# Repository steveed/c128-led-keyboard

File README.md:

# c128-led-keyboard

A mechanical keyboard for the Commodore 128 with a microcontroller on board: an ESP32-S3
scans the switches and presents them to the C128 through a CH446Q analog crosspoint, so the
computer sees an ordinary keyboard matrix while the board adds per-key RGB lighting, lock
keys that remember their state, a rear-exit connector in stock C128 pin order and, later, a
command layer, USB keyboard mode and a network keyboard.

The plate, a 1.5 mm aluminum PCB with stabilizer slots for a 9u or a 6.25u spacebar:

Renders are regenerated by GitHub Actions whenever the board or plate changes on `main`
(`make render` does the same locally, in KiCad's container).

Status (2026-11-23): schematic passing ERC; **board laid out, fully routed and DRC clean**,
with the JLCPCB order files (gerbers, BOM, placement) generated and checked in the fab's
placement preview; plate ready as one aluminum board that takes either spacebar.  Quoted at
about 500 USD for five assembled boards shipped, plus about 50 USD for the plate; not ordered
yet.  Bench firmware runs on a devkit; the bench proofs have not started.  The plan and its reasoning are in [docs/rev3-plan.md](docs/rev3-plan.md).

## What is here

| folder | what |
|---|---|
| [`pcb/`](pcb/README.md) | KiCad 10 project for the board (generated schematic, BOM), the plate as an aluminum-PCB board (takes a 9u or a 6.25u spacebar), JLCPCB order files, bench notes for proving the circuit |
| [`layout/`](pcb/README.md#layout-data) | the switch positions, matrix nets and plate outline every generator reads |
| [`firmware/`](firmware/README.md) | ESP-IDF project for the ESP32-S3, built in Docker, with a Wokwi simulation |
| [`printables/`](printables/spacebar_offset_adapter/README.md) | the spacebar offset adapter: the C128's own spacebar on the board's 9u stabilizers |
| [`keycaps/`](keycaps/README.md) | legend map, front-legend artwork and vendor notes for an MX keycap set, and the 9u spacebar drawing |
| [`docs/`](docs/) | the rev 3 plan, a part-by-part circuit walkthrough, and the rev 2.3 issues that motivated it |

The case for the 128D / DCR external keyboard is its own project,
[c128d-keyboard-case](https://github.com/steveed/c128d-keyboard-case).

## Where the measurements come from

This board is new, but the keyboard it describes is not.  The key positions, the C128 matrix
assignment of every key and the plate are, for now, the measurements of the rev 2.3 board and
plate from [the-c128-keyboard-project](https://codeberg.org/jflitton/the-c128-keyboard-project).
They were extracted once into `layout/switches.json` and `layout/plate.json`, and nothing here
reads the original files.  When the new board is laid out, `pcb/tools/extract_layout.py`
re-extracts the switches from it and the plate, firmware keymap and schematic follow; see
[pcb/README.md](pcb/README.md#layout-data).

## Parts from the original project

Some pieces are used as they are and are not copied here:

- keycap adapters for reusing the original Mitsumi caps on MX-style switches, switch shims,
  and the keyboard cable ends:
  [`printable_parts/`](https://codeberg.org/jflitton/the-c128-keyboard-project/src/branch/main/printable_parts)
- the original steel plate for laser cutting:
  [`plate/plate.step`](https://codeberg.org/jflitton/the-c128-keyboard-project/src/branch/main/plate/plate.step)
- the rev 2.3 passive board, which the bench notes use as a test bed:
  [`pcb/`](https://codeberg.org/jflitton/the-c128-keyboard-project/src/branch/main/pcb)

## Datasheets

- CH446Q analog crosspoint (WCH): <https://www.wch-ic.com/downloads/CH446DS1_PDF.html>
- M5Stack NeoPixel / RGB LED units (SK6812), used on the bench:
  <https://docs.m5stack.com/en/unit/neopixel>, <https://docs.m5stack.com/en/unit/rgb>
- Every part the board's footprints, pinouts and fab placement were checked against:
  [pcb/datasheets/README.md](pcb/datasheets/README.md)

## License and credits

This project is a fork of
[the-c128-keyboard-project](https://codeberg.org/jflitton/the-c128-keyboard-project) by
Jeff Flitton, whose PCB was in turn based on the
[original C128 keyboard PCB](https://codeberg.org/jgrip/c128-keyboard) by Johan Grip, maker
of the [C128 Neo](https://c128.se/).  The key layout, matrix assignment and plate
measurements in `layout/`, and everything generated from them, derive from Jeff Flitton's
rev 2.3 board and plate.  The rev 3 circuit, generators, firmware, keycap work and
documentation were written for this repository; none of it is part of the upstream
project, and this project is not endorsed by its authors.

Released, like the project it builds on, under
[Creative Commons Attribution-ShareAlike 4.0 International](LICENSE.md): you may copy,
modify and sell it, including boards and kits, provided you credit the authors, link back,
say what you changed, and release adaptations under the same license.  It is provided as
is, without warranties; see the license for the disclaimer.

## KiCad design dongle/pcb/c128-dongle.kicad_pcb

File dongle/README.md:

# C128D wireless dongle

A small board that plugs into the 128D's keyboard socket (on the computer's right side) and
passes the keyboard straight through.  An ESP32-S3 on it drives a CH446Q crosspoint on the
host lines, so keys can come from the rev 3 keyboard over the radio, from an app on a Mac
(USB-C), or from a USB keyboard (USB-A).  The plan and every decision behind it are in
[docs/wireless-128d.md](../docs/wireless-128d.md).

Status (2026-11-27): **schematic generated and ERC-clean; footprints drawn; board placed and
routed (autorouted, the USB nets at J1 and U5 finished by hand); DRC clean and matching the
schematic; firmware not started.**

## Files

| File | What |
|---|---|
| `pcb/tools/gen_sch.py` | writes the schematic: `c128-dongle.kicad_sch`, `mcu.kicad_sch`, `host.kicad_sch`, the project symbol library and both library tables |
| `pcb/c128-dongle.kicad_sch` | root sheet |
| `pcb/mcu.kicad_sch` | ESP32-S3-MINI-1, USB-C and USB-A behind the CH442E switch, the SY6280AAC USB-A power switch, the 5 V entry and the 3.3 V LDO, status LED, buttons, UART pads |
| `pcb/host.kicad_sch` | the keyboard's crosspoint circuit (CH446Q, lock-line and RESTORE FETs, sense diode, LED buffer) and the two DB25s |
| `pcb/c128rev3.kicad_sym`, `pcb/sym-lib-table` | project symbols: CH446Q, CH442E, SY6280AAC |
| `pcb/fp-lib-table` | the keyboard's footprint library (for the USB-C) and `dongle.pretty` |
| `pcb/tools/gen_board.py` | writes `c128-dongle.kicad_pro` and `.kicad_dru` from the keyboard's (same rules, the dongle's sheets and power nets), and once the 65 x 45 mm 4-layer board with its outline; it will not overwrite the board |
| `pcb/c128-dongle.kicad_pro`, `.kicad_dru`, `.kicad_pcb` | the project, its J1 USB-C rule, and the board (hand-edited from here: F8 brings the parts in) |
| `pcb/tools/gen_fp.py` | writes the two edge-straddle DB25 footprints into `dongle.pretty` |
| `pcb/dongle.pretty/` | the USB-A (JLCPCB's own C8328 footprint, via easyeda2kicad 1.0.1, checked against the datasheet; peg holes made non-plated, shell pads named SH) and the two DB25s (from `gen_fp.py`) |

## The schematic is generated

```
docker compose run --rm -e KICAD_SYMBOLS=/usr/share/kicad/symbols kicad python3 dongle/pcb/tools/gen_sch.py
```

Change the script, not the sheets: every run rewrites them.  The host side is not copied from
the keyboard but called: the script imports `pcb/tools/gen_sch.py` and runs its
`crosspoint_core()`, so the CH446Q, the FETs, the sense diode and the LED buffer are the same
parts, references and nets on both boards, on the same ESP32 pins.  The two DB25s take their
pin assignment from the keyboard's `HOST_PINS` table, converted to D-sub numbering.

## The DB25 footprints

`docker compose run --rm kicad python3 dongle/pcb/tools/gen_fp.py` writes both, from FCI drawing
C-DSUB-0064 (`pcb/datasheets/FCI-C-DSUB-0064.pdf`), size 25: 2.76 mm pitch, 2.84 mm between the
cup rows (a 1.6 mm board fits between them), cups about 7.4 mm behind the insulator.

- Pins 1-13 on F.Cu, pins 14-25 on B.Cu, offset half a pitch; pads 1.5 x 4.5 mm from 0.4 mm
  inside the board edge (y = 0 in the footprint; the connector hangs off at y < 0).
- Seen from the solder side with the 13-pin row on top, a plug has pin 1 on the right and a
  socket on the left, so `DB25_Pins_*` (J2) has pin 1 at +x and `DB25_Socket_*` (J3) at -x.
- The D shell goes in one way only, so the 128D's socket decides which way up the dongle
  sits: with its 13-pin row at the top, the dongle's F.Cu face is up.
- Fab: insulator, flange with its jackscrew holes (47.04 mm apart) and the D shell; a dashed
  line on Dwgs.User marks the board edge.

## The board

- **Outline:** 65 x 45 mm (widened from 60 on 2026-11-27 for room round U5 and the USB-C pair), 1 mm corners; DB25s on the west and east edges, USB on the north,
  the ESP32's antenna over the south edge (`gen_board.py`).
- **Stackup:** F.Cu signals and ICs; In1.Cu a solid GND plane; In2.Cu a third signal layer;
  B.Cu signals and the discretes.  +3V3 runs as 0.5 mm tracks.  With In2 as a +3V3 plane
  instead, the 25 straight-through DB25 lines and the CH446Q's 19 left 21-28 nets that would
  not route on two signal layers; with three, only the USB nets at J1 and the CH442E were left
  (the USB-C's A/B crossing is hand-routed, as on the keyboard).
- **Placement:** the connectors, the ESP32, the buttons and the status LED placed by hand and
  locked; the rest by KiCadRoutingTools' placer (`krt` container) with ICs on top and the
  resistors, capacitors, transistors and diodes underneath at 0 or 90 degrees, each IC's
  decaps under it.  Seed 0 of 12 (second round, `build/placement-dongle/round2/`, not
  committed), judged by a quick route; Q2 then moved clear of J3's courtyard, which the
  placer's legality check missed.
- **Silkscreen:** `docker compose run --rm kicad python3 pcb/tools/silk.py
  dongle/pcb/c128-dongle.kicad_pcb` (the keyboard's tool) moved the references DRC flagged,
  put TP2's, R1's and LED1's pin-1 mark on the fab layer (no clear spot near them), and trimmed
  J4's flange and U1's antenna outline where they run past the board edge, and J4's lines over
  its shield pads.  So J4 no longer matches its library copy (a DRC warning): don't update it
  from the library, or rerun `silk.py` after.
- **In1 is the plane only:** after hand routing, check nothing landed on In1 and no via is
  blind (both happened once).  GND is in the Power class, 0.5 mm: pick 0.25 mm before routing
  from U5's 0.35 mm GND pads, or the router won't start.
- **Connector clearances:** J4 (USB-A) at x 123 and J1 (USB-C) at x 146 leave 8.3 and 3.3 mm
  to the DB25 pad strips; the buttons are turned 90 degrees for 3.6 mm.  J4's EasyEDA courtyard
  did not cover its shell tabs and was widened.

## Ordering

```
docker compose run --rm -e KICAD_CLI=kicad-cli kicad python3 pcb/tools/fab.py dongle/pcb/c128-dongle.kicad_pcb
```

writes `dongle/pcb/fab/` (untracked): the gerbers zip, BOM and CPL, as for the keyboard (see
`pcb/README.md`).  J2 and J3, the DB25s, are left to the builder.  Order a 4-layer board with
assembly on both sides.  Rotations were checked in JLCPCB's placement preview on 2026-11-27: the
bottom side as written, the top with the corrections in `fab.py`'s `ROT_ADD_TOP` (U2-U8).
U3's and U5's turn ("right 90" in the preview, taken as clockwise) is still to be confirmed on
the next upload.  Quoted that day for five: about 175 USD for boards and assembly, plus 127 USD
shipping and tariffs; to be ordered with the keyboard's next order to share the shipping.

## Parts this board adds

LCSC numbers are in the script; check each on lcsc.com before ordering.

| Part | LCSC | Datasheet checked |
|---|---|---|
| ESP32-S3-MINI-1-N8 (PCB antenna) | C2913206 | |
| WCH CH442E, USB 2.0 2:1 switch | C150097 | `pcb/datasheets/C150097.pdf` (WCH CH440/CH442 v3B): pins, select polarity, runs at 3.3 V |
| Silergy SY6280AAC, USB-A power switch | C55136 | `pcb/datasheets/C55136.pdf` (preliminary rev 0.3): pins, Ilim = 6800 / Rset, EN active high |
| USB-A receptacle, right angle (Jing Extension 904-131A2032S10100) | C8328 | `pcb/datasheets/C8328.pdf`: pins, outline, PCB layout (signal-pad width not dimensioned) |
| UNI-ROYAL 12 k, 0603, 1 % (the SY6280's Rset, about 0.57 A) | C22790 | `pcb/datasheets/C22790.pdf` (series sheet); value from the LCSC page |
| DB25 male and female, solder cup | none | hand-soldered; straddle 1.6 mm board edges |

## Still open

- **Power:** the 128D's +5 V on the keyboard socket feeds the dongle, with the ESP32's radio
  peaks and a USB keyboard on top of the keyboard's own draw.  Measure what the 128D's
  keyboard 5 V delivers before relying on it without the USB-C.
- **Routing:** KiCadRoutingTools' router (`krt`): `route_diff.py` for the three USB pairs, then
  `route.py` on F.Cu, In2 and B.Cu at the board's rules (`--escalation board
  --no-fix-drc-settings`).  It cannot do the USB-C pair at J1 legally: J1's D+/D- pads are 0.3 mm
  wide, and the pair pass drops a 0.3/0.15 mm via into the pad to change layers (its own log calls
  it an advanced-tier fab floor), so that pair is hand-routed, with the A6/B6 and A7/B7 crossing.
  U5 sits between the USB-A and the USB-C, just in from the north edge (139, 83), where its
  lines to both ports are shortest.  The USB-C pair's layer change beside J1, its A7/B7 crossing
  and the last stubs into U5 were routed by hand.
- **Firmware:** the dongle app, sharing the keyboard firmware's crosspoint driver.

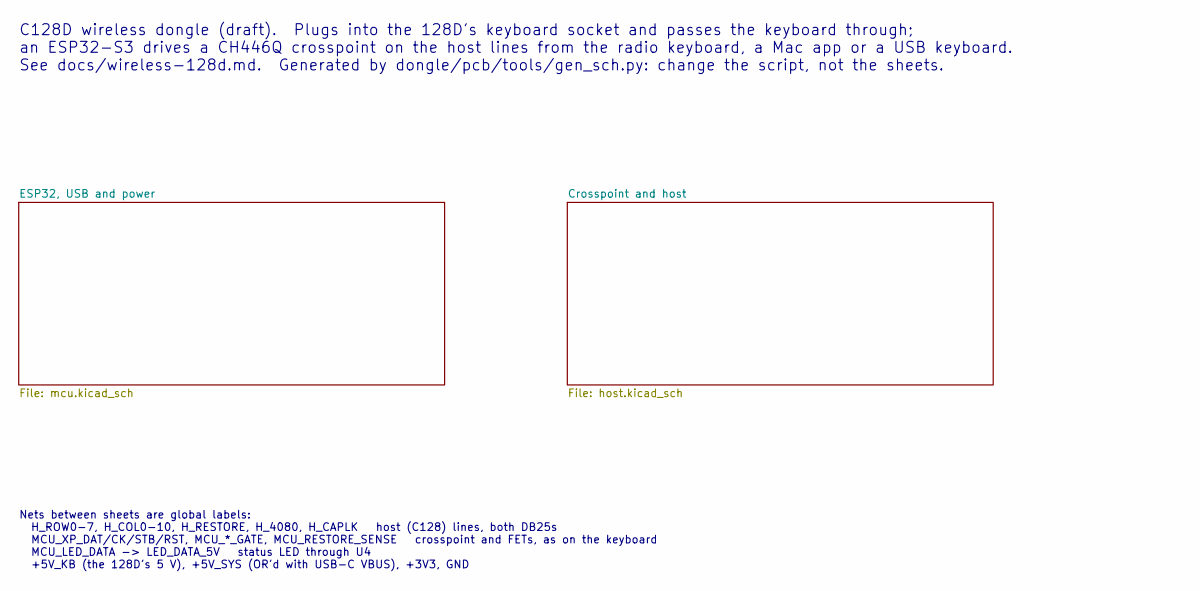
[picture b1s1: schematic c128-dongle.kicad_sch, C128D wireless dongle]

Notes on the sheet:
C128D wireless dongle (draft). Plugs into the 128D's keyboard socket and passes the keyboard through; an ESP32-S3 drives a CH446Q crosspoint on the host lines from the radio keyboard, a Mac app or a USB keyboard. See docs/wireless-128d.md. Generated by dongle/pcb/tools/gen_sch.py: change the script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
Nets between sheets are global labels: H_ROW0-7, H_COL0-10, H_RESTORE, H_4080, H_CAPLK host (C128) lines, both DB25s MCU_XP_DAT/CK/STB/RST, MCU_*_GATE, MCU_RESTORE_SENSE crosspoint and FETs, as on the keyboard MCU_LED_DATA -> LED_DATA_5V status LED through U4 +5V_KB (the 128D's 5 V), +5V_SYS (OR'd 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

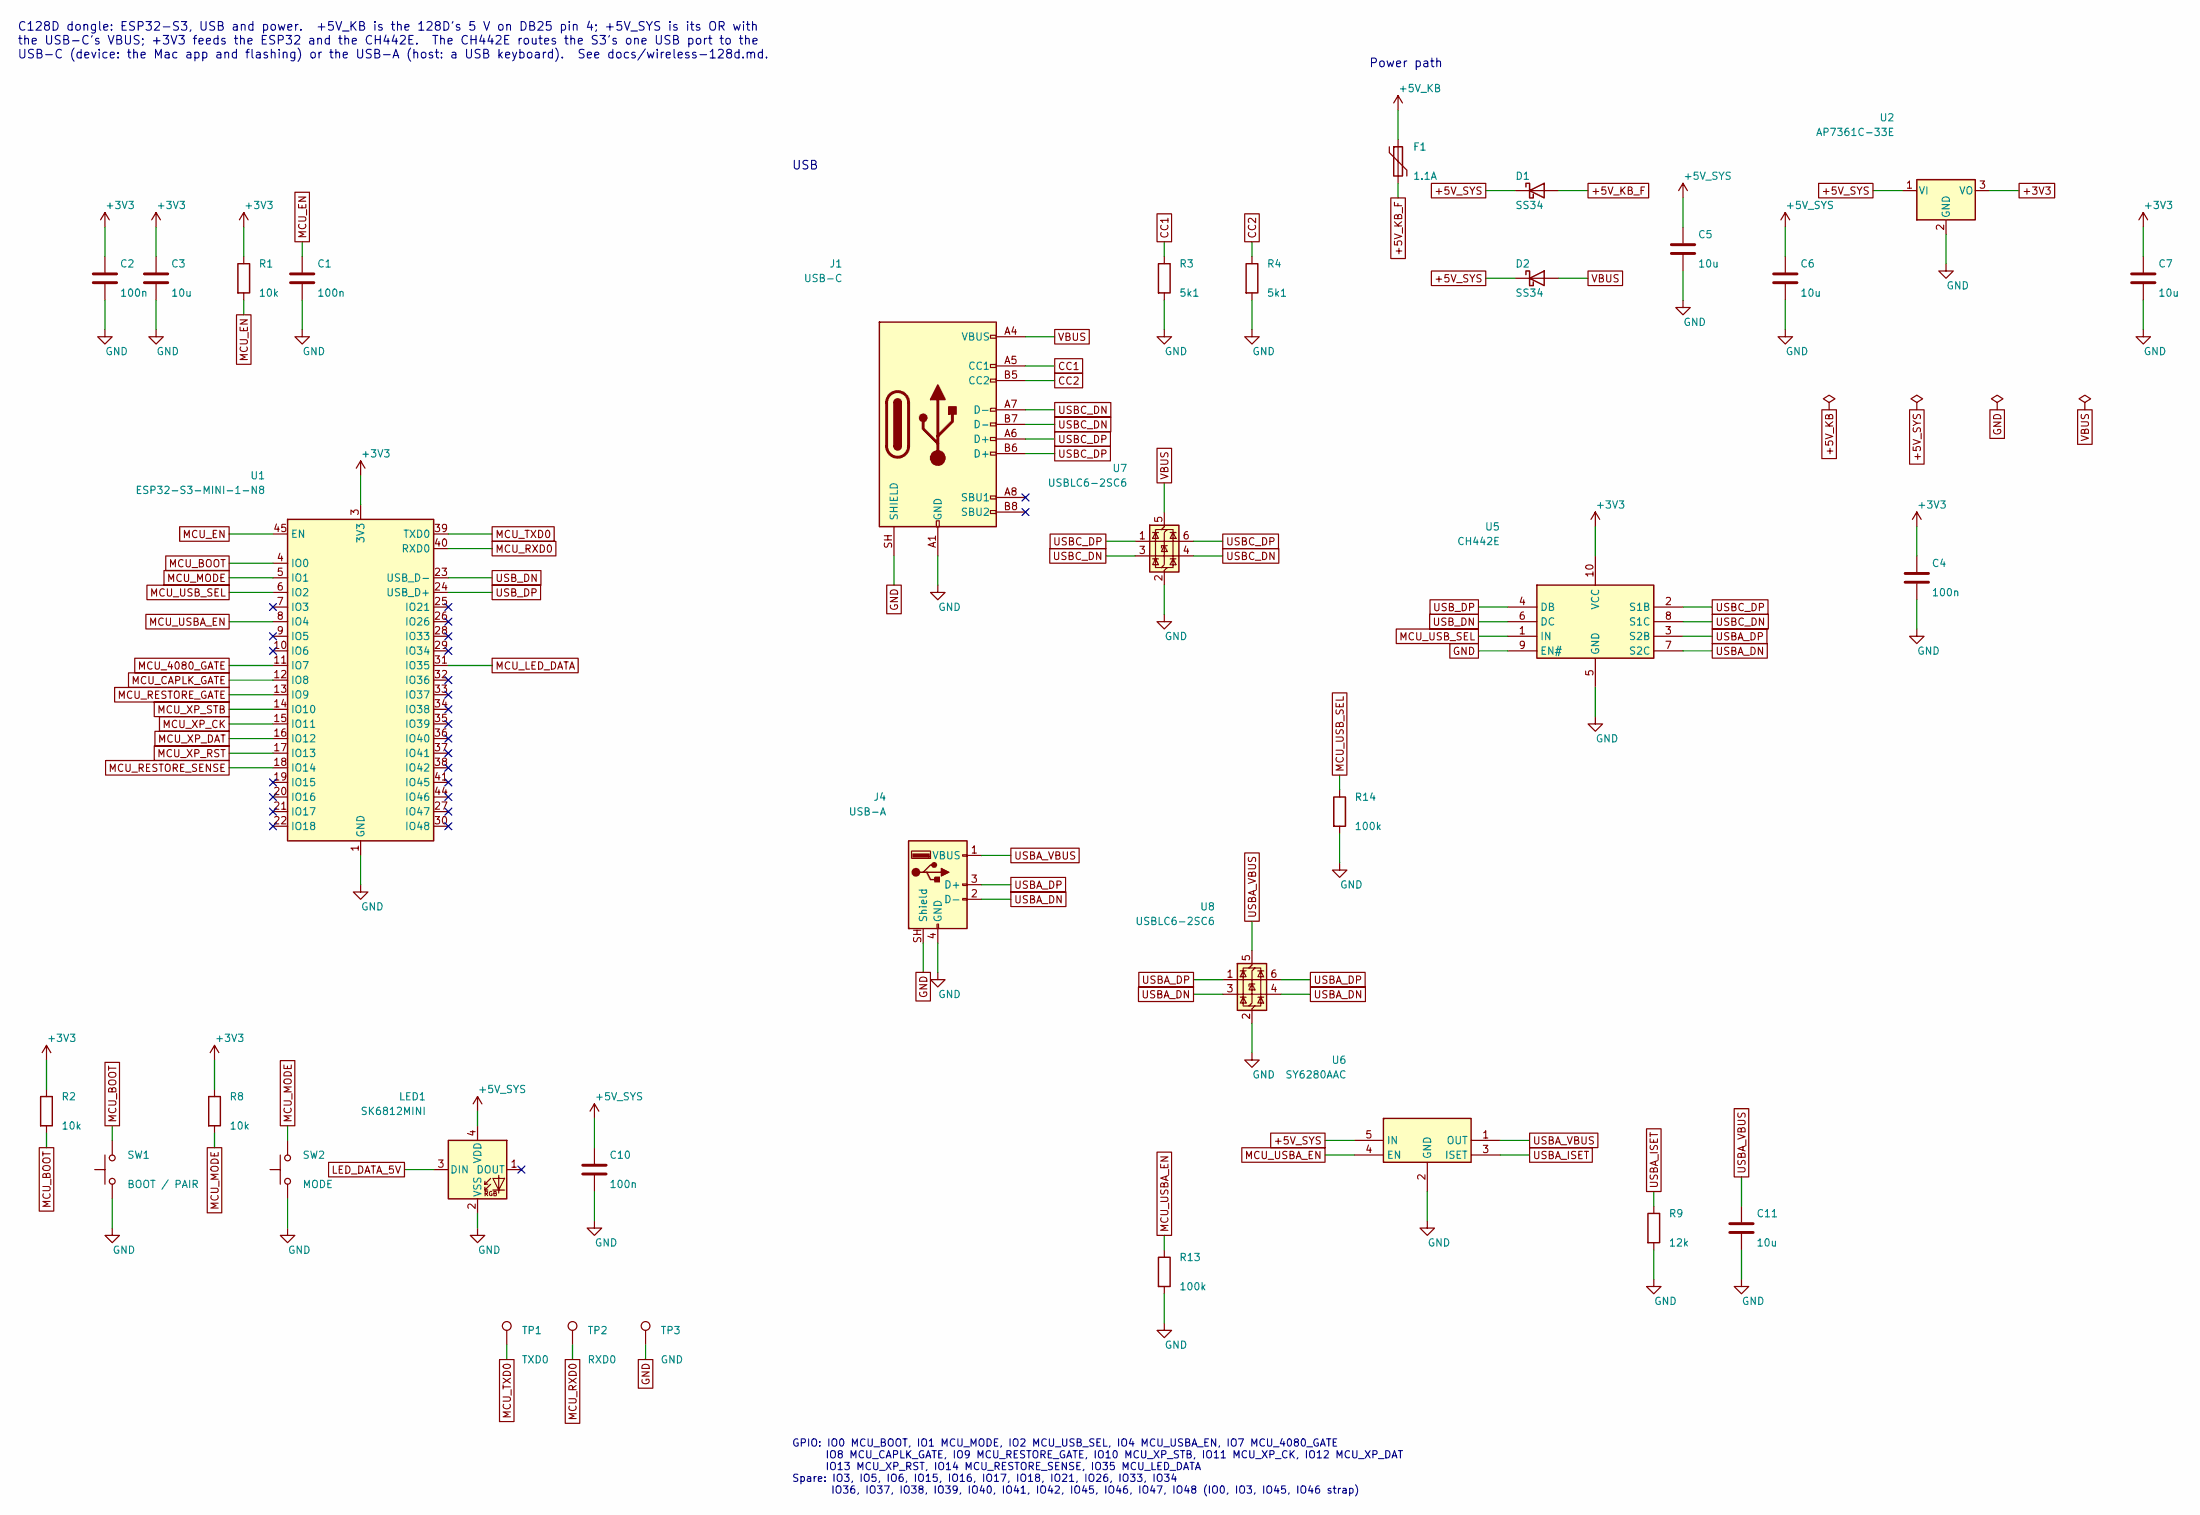
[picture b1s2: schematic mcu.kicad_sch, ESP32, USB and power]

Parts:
C1, C2, C4, C10: 100n; C_0603_1608Metric_Pad1.08x0.95mm_HandSolder; LCSC C14663
C3: 10u; C_0603_1608Metric_Pad1.08x0.95mm_HandSolder; LCSC C19702
C5, C6, C7, C11: 10u; C_1206_3216Metric_Pad1.33x1.80mm_HandSolder; LCSC C13585
D1, D2: SS34; D_SMA; LCSC C8678
F1: 1.1A; Fuse_1812_4532Metric; LCSC C142746
J1: USB-C; USB_C_Receptacle_ShouHan_TYPE-C-16P-3MD-040; LCSC C41417453
J4: USB-A; USB_A_Jing_904-131A2032S10100; LCSC C8328
LED1: SK6812MINI; LED_SK6812MINI_PLCC4_3.5x3.5mm_P1.75mm; LCSC C2886570
R1, R2, R8: 10k; R_0603_1608Metric_Pad0.98x0.95mm_HandSolder; LCSC C25804
R3, R4: 5k1; R_0603_1608Metric_Pad0.98x0.95mm_HandSolder; LCSC C23186
R9: 12k; R_0603_1608Metric_Pad0.98x0.95mm_HandSolder; LCSC C22790
R13, R14: 100k; R_0603_1608Metric_Pad0.98x0.95mm_HandSolder; LCSC C25803
SW1: BOOT / PAIR; SW_SPST_PTS645Sx43SMTR92; LCSC C221880
SW2: MODE; SW_SPST_PTS645Sx43SMTR92; LCSC C221880
TP1: TXD0; TestPoint_Pad_1.0x1.0mm
TP2: RXD0; TestPoint_Pad_1.0x1.0mm
TP3: GND; TestPoint_Pad_1.0x1.0mm
U1: ESP32-S3-MINI-1-N8; ESP32-S2-MINI-1; LCSC C2913206
U2: AP7361C-33E; SOT-223-3_TabPin2; LCSC C500795
U5: CH442E; MSOP-10_3x3mm_P0.5mm; LCSC C150097
U6: SY6280AAC; SOT-23-5; LCSC C55136
U7, U8: USBLC6-2SC6; SOT-23-6; LCSC C7519

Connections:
+3V3: C2.1, C3.1, C4.1, C7.1, R1.1, R2.1, R8.1, U1.3 (3V3), U2.3 (VO), U5.10 (VCC); also elsewhere on the board
+5V_KB: F1.1; also elsewhere on the board
+5V_KB_F: D1.2 (A), F1.2
+5V_SYS: C5.1, C6.1, C10.1, D1.1 (K), D2.1 (K), LED1.4 (VDD), U2.1 (VI), U6.5 (IN); also elsewhere on the board
CC1: J1.A5 (CC1), R3.1
CC2: J1.B5 (CC2), R4.1
GND: C1.2, C2.2, C3.2, C4.2, C5.2, C6.2, C7.2, C10.2, C11.2, J1.A1 (GND), J1.A12 (GND), J1.B1 (GND), J1.B12 (GND), J1.SH (SHIELD), J4.4 (GND), J4.SH (Shield), LED1.2 (VSS), R3.2, R4.2, R9.2, R13.2, R14.2, SW1.1, SW2.1, TP3.1 (1_1), U1.1 (GND), U1.2 (GND), U1.42 (GND), U1.43 (GND), U1.46 (GND), U1.47 (GND), U1.48 (GND), U1.49 (GND), U1.50 (GND), U1.51 (GND), U1.52 (GND), U1.53 (GND), U1.54 (GND), U1.55 (GND), U1.56 (GND), U1.57 (GND), U1.58 (GND), U1.59 (GND), U1.60 (GND), U1.61 (GND), U1.62 (GND), U1.63 (GND), U1.64 (GND), U1.65 (GND), U2.2 (GND), U5.5 (GND), U5.9 (EN#), U6.2 (GND), U7.2 (GND), U8.2 (GND); also elsewhere on the board
LED_DATA_5V: LED1.3 (DIN); also elsewhere on the board
MCU_4080_GATE: U1.11 (IO7); also elsewhere on the board
MCU_BOOT: R2.2, SW1.2, U1.4 (IO0)
MCU_CAPLK_GATE: U1.12 (IO8); also elsewhere on the board
MCU_EN: C1.1, R1.2, U1.45 (EN)
MCU_LED_DATA: U1.31 (IO35); also elsewhere on the board
MCU_MODE: R8.2, SW2.2, U1.5 (IO1)
MCU_RESTORE_GATE: U1.13 (IO9); also elsewhere on the board
MCU_RESTORE_SENSE: U1.18 (IO14); also elsewhere on the board
MCU_RXD0: TP2.1 (1_1), U1.40 (RXD0)
MCU_TXD0: TP1.1 (1_1), U1.39 (TXD0)
MCU_USBA_EN: R13.1, U1.8 (IO4), U6.4 (EN)
MCU_USB_SEL: R14.1, U1.6 (IO2), U5.1 (IN)
MCU_XP_CK: U1.15 (IO11); also elsewhere on the board
MCU_XP_DAT: U1.16 (IO12); also elsewhere on the board
MCU_XP_RST: U1.17 (IO13); also elsewhere on the board
MCU_XP_STB: U1.14 (IO10); also elsewhere on the board
USBA_DN: J4.2 (D-), U5.7 (S2C), U8.3 (I/O2), U8.4 (I/O2)
USBA_DP: J4.3 (D+), U5.3 (S2B), U8.1 (I/O1), U8.6 (I/O1)
USBA_ISET: R9.1, U6.3 (ISET)
USBA_VBUS: C11.1, J4.1 (VBUS), U6.1 (OUT), U8.5 (VBUS)
USBC_DN: J1.A7 (D-), J1.B7 (D-), U5.8 (S1C), U7.3 (I/O2), U7.4 (I/O2)
USBC_DP: J1.A6 (D+), J1.B6 (D+), U5.2 (S1B), U7.1 (I/O1), U7.6 (I/O1)
USB_DN: U1.23 (USB_D-), U5.6 (DC)
USB_DP: U1.24 (USB_D+), U5.4 (DB)
VBUS: D2.2 (A), J1.A4 (VBUS), J1.A9 (VBUS), J1.B4 (VBUS), J1.B9 (VBUS), U7.5 (VBUS)

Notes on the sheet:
C128D dongle: ESP32-S3, USB and power. +5V_KB is the 128D's 5 V on DB25 pin 4; +5V_SYS is its OR with the USB-C's VBUS; +3V3 feeds the ESP32 and the CH442E. The CH442E routes the S3's one USB port to the USB-C (device: the Mac app and flashing) or the USB-A (host: a USB keyboard). See docs/wireless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
USB
Power path
GPIO: IO0 MCU_BOOT, IO1 MCU_MODE, IO2 MCU_USB_SEL, IO4 MCU_USBA_EN, IO7 MCU_4080_GATE IO8 MCU_CAPLK_GATE, IO9 MCU_RESTORE_GATE, IO10 MCU_XP_STB, IO11 MCU_XP_CK, IO12 MCU_XP_DAT IO13 MCU_XP_RST, IO14 MCU_RESTORE_SENSE, IO35 MCU_LED_DATA Spare: IO3, IO5, IO6, IO15, IO16, IO17, IO18, IO21, IO26, IO33,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

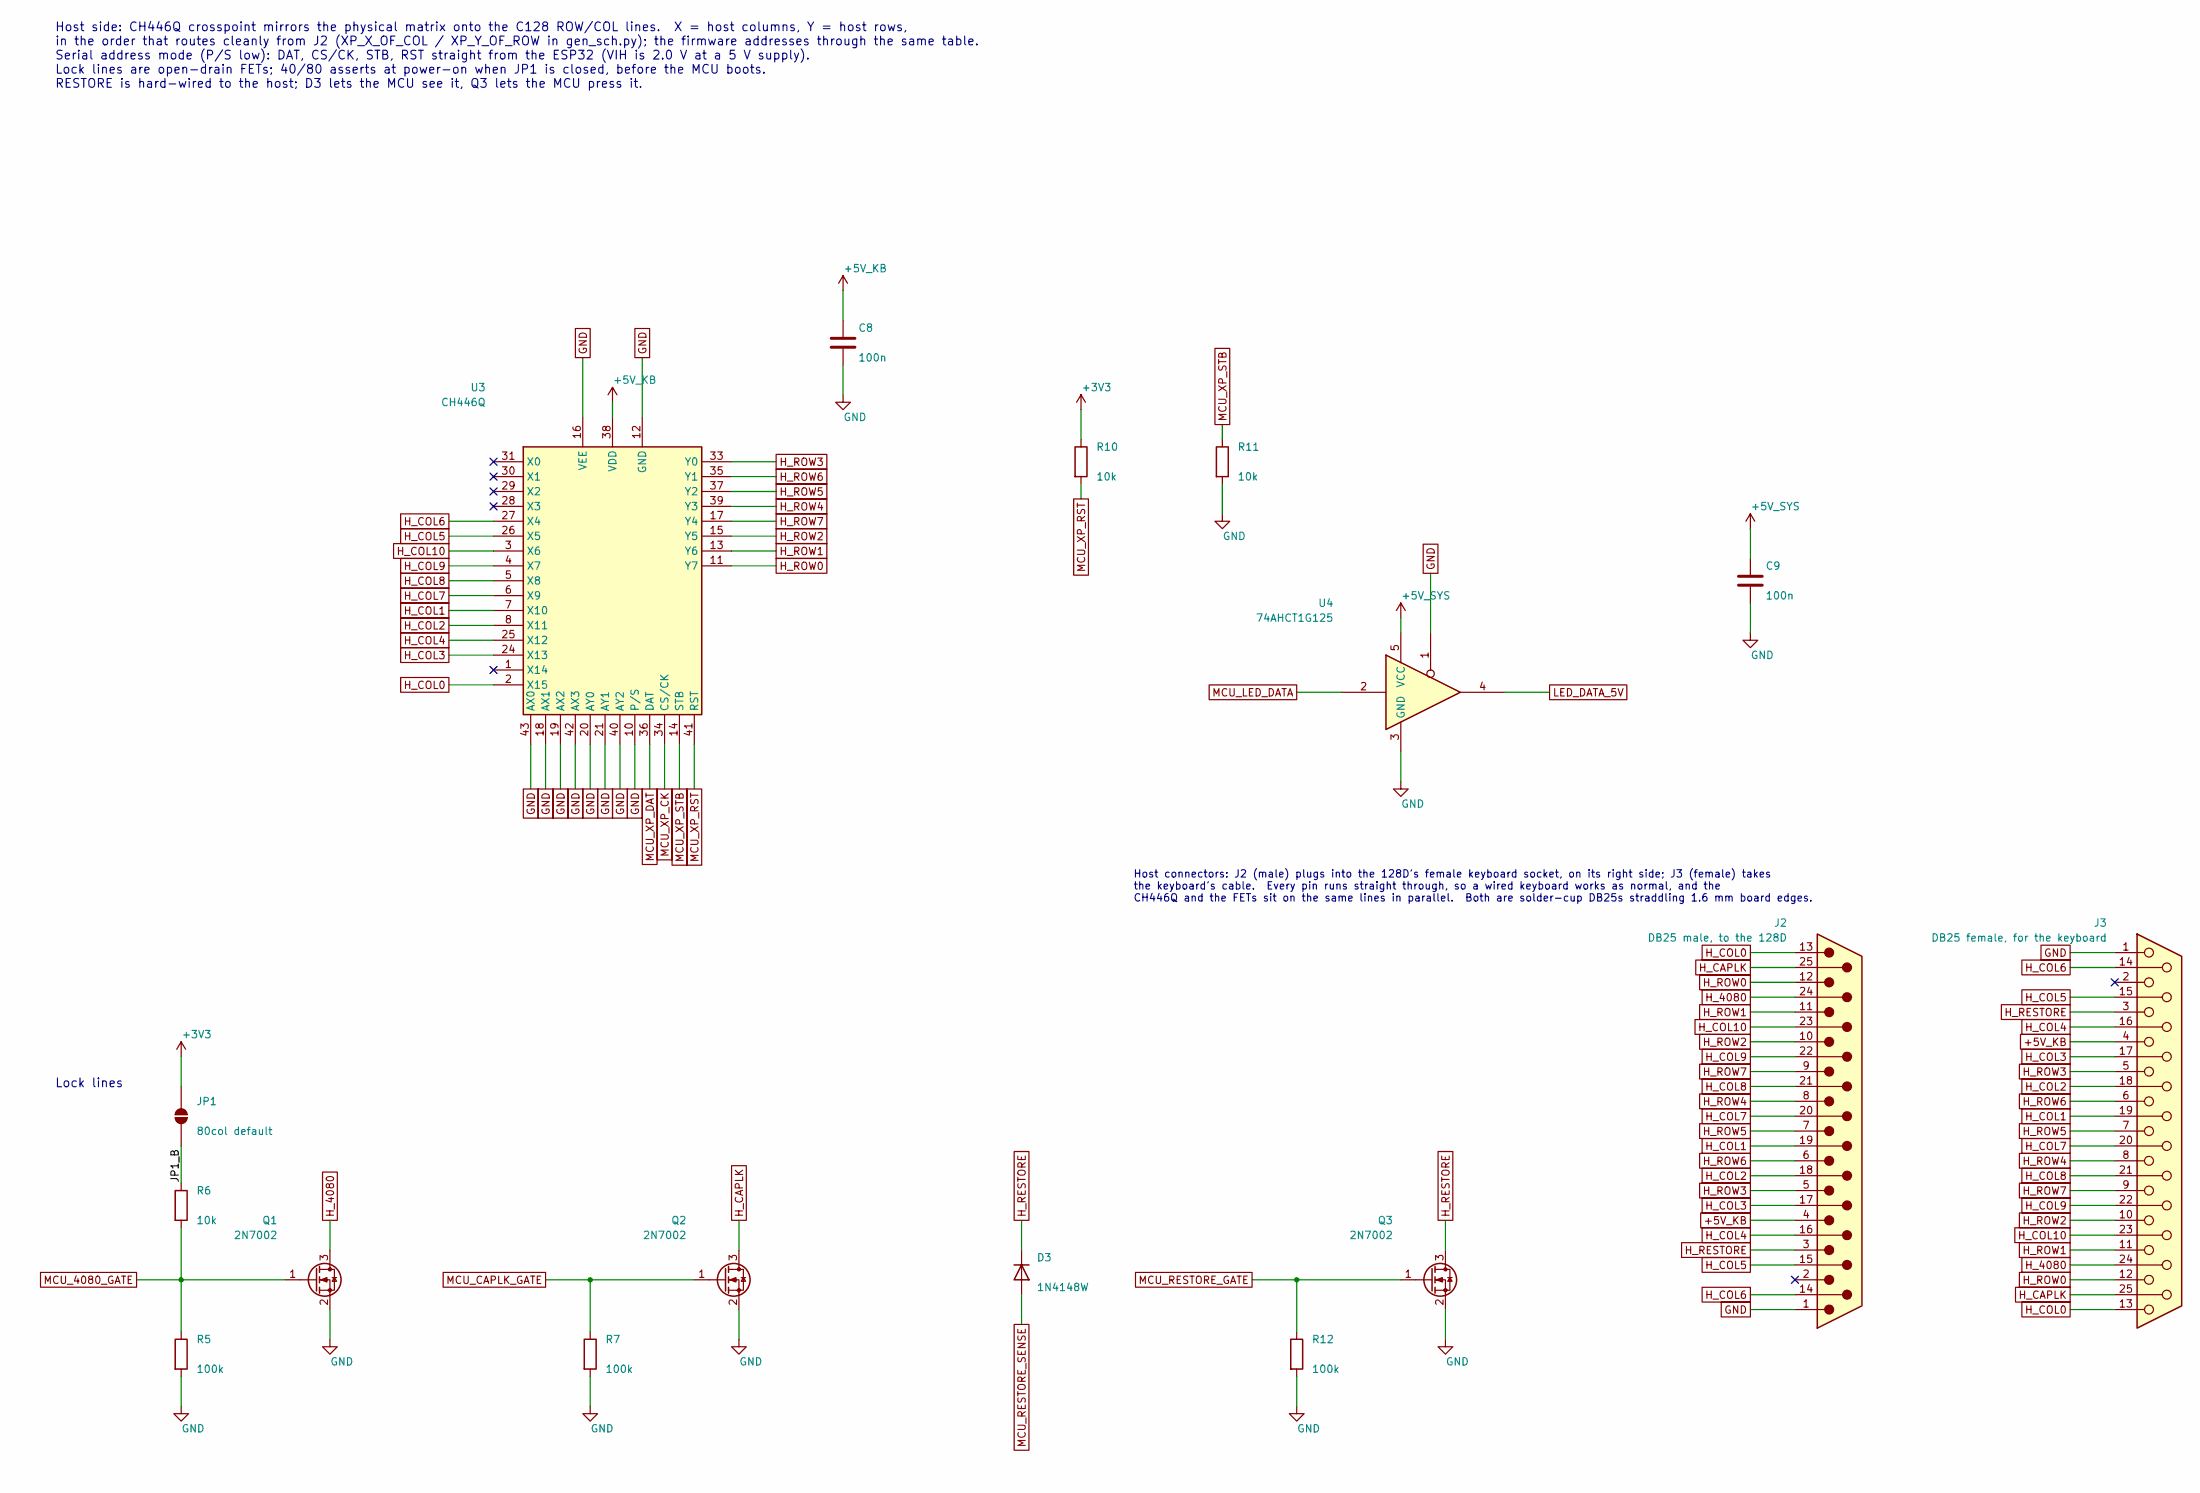
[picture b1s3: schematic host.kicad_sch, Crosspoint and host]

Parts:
C8, C9: 100n; C_0603_1608Metric_Pad1.08x0.95mm_HandSolder; LCSC C14663
D3: 1N4148W; D_SOD-123; LCSC C81598
J2: DB25 male, to the 128D; DB25_Pins_EdgeStraddle_1.6mm
J3: DB25 female, for the keyboard; DB25_Socket_EdgeStraddle_1.6mm
JP1: 80col default; SolderJumper-2_P1.3mm_Open_RoundedPad1.0x1.5mm
Q1, Q2, Q3: 2N7002; SOT-23; LCSC C8545
R5, R7, R12: 100k; R_0603_1608Metric_Pad0.98x0.95mm_HandSolder; LCSC C25803
R6, R10, R11: 10k; R_0603_1608Metric_Pad0.98x0.95mm_HandSolder; LCSC C25804
U3: CH446Q; LQFP-44_10x10mm_P0.8mm; LCSC C109471
U4: 74AHCT1G125; SOT-23-5; LCSC C7484

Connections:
+3V3: JP1.2 (B), R10.1; also elsewhere on the board
+5V_KB: C8.1, J2.4, J3.4, U3.38 (VDD); also elsewhere on the board
+5V_SYS: C9.1, U4.5 (VCC); also elsewhere on the board
/Crosspoint and host/JP1_B: JP1.1 (A), R6.1
GND: C8.2, C9.2, J2.1, J3.1, Q1.2 (S), Q2.2 (S), Q3.2 (S), R5.2, R7.2, R11.2, R12.2, U3.10 (P/S), U3.12 (GND), U3.16 (VEE), U3.18 (AX1), U3.19 (AX2), U3.20 (AY0), U3.21 (AY1), U3.40 (AY2), U3.42 (AX3), U3.43 (AX0), U4.1, U4.3 (GND); also elsewhere on the board
H_4080: J2.24, J3.24, Q1.3 (D)
H_CAPLK: J2.25, J3.25, Q2.3 (D)
H_COL0: J2.13, J3.13, U3.2 (X15)
H_COL1: J2.19, J3.19, U3.7 (X10)
H_COL2: J2.18, J3.18, U3.8 (X11)
H_COL3: J2.17, J3.17, U3.24 (X13)
H_COL4: J2.16, J3.16, U3.25 (X12)
H_COL5: J2.15, J3.15, U3.26 (X5)
H_COL6: J2.14, J3.14, U3.27 (X4)
H_COL7: J2.20, J3.20, U3.6 (X9)
H_COL8: J2.21, J3.21, U3.5 (X8)
H_COL9: J2.22, J3.22, U3.4 (X7)
H_COL10: J2.23, J3.23, U3.3 (X6)
H_RESTORE: D3.1 (K), J2.3, J3.3, Q3.3 (D)
H_ROW0: J2.12, J3.12, U3.11 (Y7)
H_ROW1: J2.11, J3.11, U3.13 (Y6)
H_ROW2: J2.10, J3.10, U3.15 (Y5)
H_ROW3: J2.5, J3.5, U3.33 (Y0)
H_ROW4: J2.8, J3.8, U3.39 (Y3)
H_ROW5: J2.7, J3.7, U3.37 (Y2)
H_ROW6: J2.6, J3.6, U3.35 (Y1)
H_ROW7: J2.9, J3.9, U3.17 (Y4)
LED_DATA_5V: U4.4; also elsewhere on the board
MCU_4080_GATE: Q1.1 (G), R5.1, R6.2; also elsewhere on the board
MCU_CAPLK_GATE: Q2.1 (G), R7.1; also elsewhere on the board
MCU_LED_DATA: U4.2; also elsewhere on the board
MCU_RESTORE_GATE: Q3.1 (G), R12.1; also elsewhere on the board
MCU_RESTORE_SENSE: D3.2 (A); also elsewhere on the board
MCU_XP_CK: U3.34 (CS/CK); also elsewhere on the board
MCU_XP_DAT: U3.36 (DAT); also elsewhere on the board
MCU_XP_RST: R10.2, U3.41 (RST); also elsewhere on the board
MCU_XP_STB: R11.1, U3.14 (STB); also elsewhere on the board

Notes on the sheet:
Host side: CH446Q crosspoint mirrors the physical matrix onto the C128 ROW/COL lines. X = host columns, Y = host rows, in the order that routes cleanly from J2 (XP_X_OF_COL / XP_Y_OF_ROW in gen_sch.py); the firmware addresses through the same table. Serial address mode (P/S low): DAT, CS/CK, STB, R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
Lock lines
Host connectors: J2 (male) plugs into the 128D's female keyboard socket, on its right side; J3 (female) takes the keyboard's cable. Every pin runs straight through, so a wired keyboard works as normal, and the CH446Q and the FETs sit on the same lines in parallel. Both are solder-cup DB25s straddli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

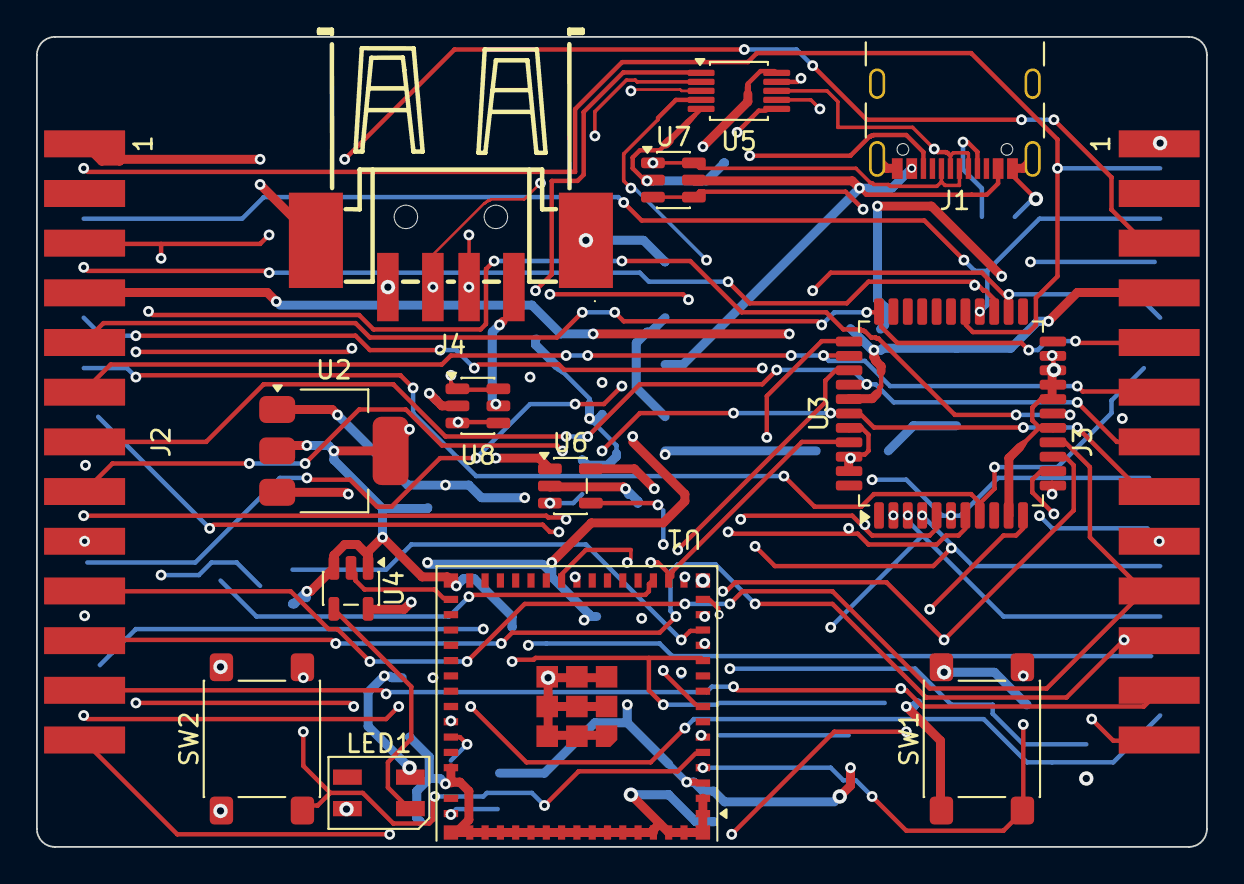
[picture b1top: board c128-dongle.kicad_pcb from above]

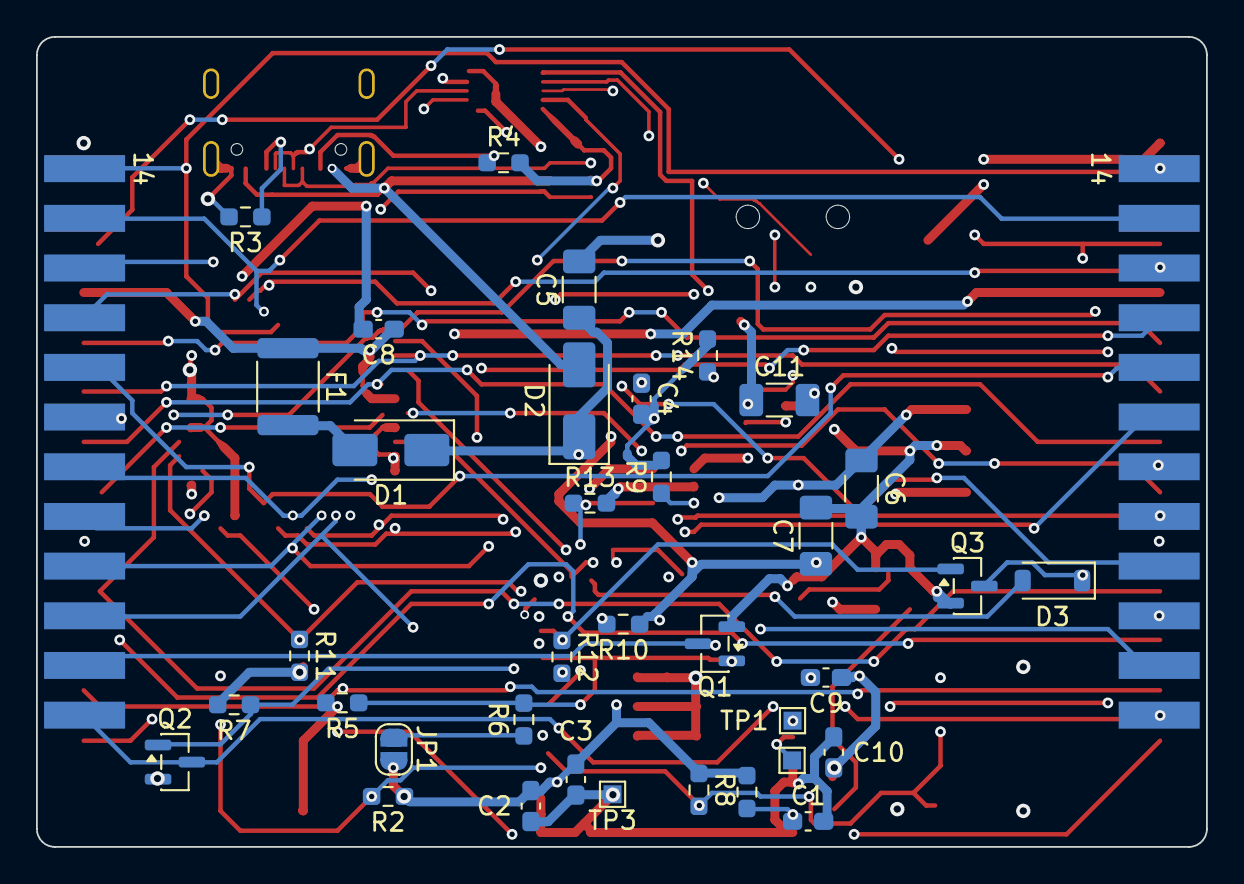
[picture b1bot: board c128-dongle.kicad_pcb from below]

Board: 4 copper layers, 65.0 x 45.0 mm, 51 parts (36 on the bottom side), 56 nets.

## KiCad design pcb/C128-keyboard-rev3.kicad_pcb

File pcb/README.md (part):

# PCB rev 3

KiCad 10 project for the smart board described in [docs/rev3-plan.md](../docs/rev3-plan.md):
ESP32-S3 module scanning the switches, a CH446Q crosspoint presenting them to the C128,
per-key SK6812 MINI lighting, saved lock state, and a rear-exit host connector in stock C128
pin order.

Status (2026-11-23): **schematic passes ERC with zero violations; the board is placed, fully
routed and tidied, with nothing unconnected, no schematic parity differences and no DRC
errors or silkscreen warnings.  The JLCPCB order files come out of `tools/fab.py`, every
SMD part has an in-stock LCSC number, and the placement rotations have been checked part by
part in JLCPCB's preview.  The dual-spacebar plate is ready to order.**  Nothing has been
ordered or built yet.
A part-by-part explanation of the circuit is in
[docs/rev3-circuit-walkthrough.md](../docs/rev3-circuit-walkthrough.md).

## Files

| File | What |
|---|---|
| `C128-keyboard-rev3.kicad_pro` / `.kicad_sch` | project and root sheet (four sub-sheets) |
| `mcu.kicad_sch` | ESP32-S3-MINI-1U-N8 (U.FL antenna), USB-C, 5 V OR-ing, AP7361C-33E LDO, buttons |
| `crosspoint.kicad_sch` | CH446Q in serial mode, 74AHCT1G125 LED-data buffer, lock-line and RESTORE FETs, RESTORE sense diode D3, host connector J2, external LED header J3 |
| `matrix.kicad_sch` | 92 switches in a 6 x 20 scanned matrix that follows the board (`tools/layout.py` `physical_matrix`), one 1N4148W per scanned key, 74HC154 plus five GPIO for the columns |
| `leds.kicad_sch` | 92 SK6812 MINI (top mount) in chain order (lock keys first) |
| `c128rev3.kicad_sym`, `sym-lib-table` | project library with the CH446Q symbol (LQFP-44 numbering) |
| `c128rev3.pretty/`, `fp-lib-table` | project footprints: MX switches (1u, 1.5u, 2u, spacebar), the SK6812 MINI for the switch LED pocket, and the USB-C receptacle |
| `datasheets/README.md` | links to the datasheets the footprints, pinouts and placement rotations were checked against; the PDFs are downloaded there by LCSC number and not tracked |
| `tools/gen_fp.py` | the generator that writes `c128rev3.pretty/` and `fp-lib-table` |
| `C128-keyboard-rev3.kicad_pcb` | the board: rev 2.3 outline, four layers, every footprint linked to the schematic, placed and routed; DRC clean |
| `tools/gen_pcb.py` | made the board's first version; the board is the source now (see *The board* below) |
| `tools/route_keys.py` | lays the regular per-key copper on the board; rerunnable (see *Routing*) |
| `tools/freeroute.py`, `tools/plane_taps.py`, `tools/clean_dangling.py` | autoroute the rest in a container; tap the inner planes from SMD pads; delete dead-end stubs (see *Routing*) |
| `tools/move.py`, `tools/swap_footprint.py`, `tools/sync_nets.py`, `tools/rip_up.py`, `tools/tidy.py`, `tools/silk.py`, `tools/to_sheet.py` | rework a routed board: move or turn parts, swap a footprint, take the schematic's nets after a change, rip up an area, tidy the router's copper, clear the silkscreen, center the board on its sheet |
| `tools/route_host.py` | lays the host lines between J2 and the CH446Q (see *Routing*) |
| `bom.csv` | grouped BOM exported from the schematic |
| `tools/fab.py`, `fab/` | the JLCPCB order files (gerber zip, BOM, placement list) and the script that writes them; `fab/` is not tracked (see *Ordering from JLCPCB*) |
| `tools/gen_sch.py`, `tools/kisym.py` | the generator that produced all of the above |
| `tools/pinmaps.json` | CH446Q LQFP-44 pin map, GPIO plan, host connector pinout |
| `bench/README.md` | shopping list and breadboard wiring to prove the design on a rev 2.3 board |
| `plate/plate-dual.kicad_pcb` | the plate to order: a KiCad board (outline polygons plus a full copper pour) for aluminum-core PCB fabrication, with stabilizer slots for both a 9u and a 6.25u spacebar; DRC clean |
| `plate/plate-9u.kicad_pcb`, `plate/plate-6.25u.kicad_pcb` | the same plate for one spacebar only |
| `plate/plate_features.json` | mounting holes, locating holes, tab slots and stabilizer cutouts in PCB coordinates, for the layout |
| `tools/plate_step.py`, `tools/gen_plate.py` | STEP reader and plate-board generator |
| `liner/` | the bottom liner: die-cut DXF, 1:1 drawing and how it fits ([liner/README.md](liner/README.md)) |
| `tools/gen_liner.py` | writes the liner from the board: outline, windows over the tall back-side parts, tape strips on bare board |
| `tools/plate_header.kicad_pcb` | the plate boards' layer stack and setup block, copied into every generated board |
| `tools/extract_layout.py`, `tools/layout.py` | write and read `../layout/`, the measurements every generator works from |

## Layout data

Every generator here, and `firmware/tools/gen_keymap.py`, reads its key positions from the
repository's `layout/` folder rather than from another board file:

- `layout/switches.json`: the 92 switches (reference, key legend, center in KiCad board
  coordinates, row and column nets).  Extracted from the rev 2.3 board,
  [`pcb/C128-keyboard.kicad_pcb`](https://codeberg.org/jflitton/the-c128-keyboard-project/src/branch/main/pcb/C128-keyboard.kicad_pcb) in the-c128-keyboard-project.
- `layout/plate.json`: the plate's outline and every cutout as line/arc loops, in the STEP
  model's own frame.  Extracted from that project's
  [`plate/plate.step`](https://codeberg.org/jflitton/the-c128-keyboard-project/src/branch/main/plate/plate.step); `gen_plate.py` fits it onto the switches.

- `layout/outline.json`: the board outline (Edge.Cuts lines and circles) from the same
  rev 2.3 board; `gen_pcb.py` drew the rev 3 outline from it.

`switches.json` also records each switch's rotation.  They are the original measurements,
used until the new board exists.  Once it is laid out,
point the extractor at it and regenerate:

```
python3 pcb/tools/extract_layout.py switches pcb/<new board>.kicad_pcb
python3 pcb/tools/gen_plate.py            # plate refits onto the new switch centers
python3 pcb/tools/gen_liner.py            # liner windows and tape follow the parts (then make liner)
python3 firmware/tools/gen_keymap.py
```

`extract_layout.py plate <file>.step` does the same for a new plate model.  Both files keep
one switch or loop per line, so a moved key is a one-line diff.

## How it was made, and how to change it

The schematic is generated: `python3 pcb/tools/gen_sch.py` rewrites every `.kicad_sch`
here.  Symbols come straight from the KiCad 10 standard libraries (derived symbols are
flattened the way eeschema does it), switch positions and matrix nets come from
`layout/switches.json` (see *Layout data* below), and all connectivity is global labels on short pin stubs.
The output is meant to be opened in eeschema and tidied by hand.  **Once hand edits start,
stop running the generator**, or fold the change into `gen_sch.py` first.

The generator writes the file-format versions KiCad 10.0 uses (`VERSION`, `LIB_VERSION` at
the top of `gen_sch.py`), so eeschema opens the sheets without asking to resave them.  When
a newer KiCad moves the format, `kicad-cli sch upgrade --force` on a copy shows the new
version number to paste in; the check that nothing else changed is to export the netlist
from both and compare.

Every UUID in the output is deterministic: symbols and pins are keyed on sheet file plus
reference designator, wires, labels and text on type and position.  Running the generator
twice gives byte-identical files, a one-part change shows up as a one-part diff, and once a
board exists its footprints stay linked to their symbols across regenerations.  Renaming a
reference designator does change that symbol's UUID, so treat refs as stable once layout
has started.

One quirk worth knowing: `kicad-cli sch erc` reports a wire that runs directly from one pin
to another as "not connected to anything", even though both pins show as connected.  The
generator therefore puts a net label on every such wire (the LED chain segments, the 74HC154
fan-out, the jumper link).  Wires that end on a label, junction or another wire are fine.

Placeholders to resolve during layout:

- Switch and LED footprints are the project's own (`tools/gen_fp.py`, run it with
  `python3 pcb/tools/gen_fp.py`).  The switches keep rev 2.3's MX pin pattern without the
  Alps pads; the LED is a separate footprint that the placement script puts at `LED_OFFSET`
  in each switch's frame, opposite the pins where rev 2.3 had its lock-key LED holes.
  `LED_OFFSET` (0, 5.08) is **provisional** until the Outemu LED pocket is measured
  (bench/before-parts-arrive.md section 5).  The LED footprint has no courtyard on purpose:
  it sits inside the switch's.
- Spacebar stabilizer spacing (`SPACEBAR_STABS` in `gen_fp.py`): standard MX, 100 mm (6.25u)
  and 133.35 mm (9u), matching both plates and the 9u keycap drawing.  Decided 2026-11-21.
  The original C128 spacebar on its adapters wants the narrower 125.35 mm the rev 2.3 board
  drilled (and 99.77 mm for its 6.25u set); 125.35 and 133.35 are 4 mm apart, so one
  footprint cannot carry both, and rev 3 drills for standard MX spacebars.  The original bar
  goes on the 133.35 mm stabilizers through
  [`printables/spacebar_offset_adapter`](../printables/spacebar_offset_adapter/README.md),
  which moves each stabilizer stem 4 mm outward (tested 2026-11-23).
- USB-C is the SHOU HAN TYPE-C 16P 3MD 040 (LCSC C41417453; datasheet linked in `datasheets/README.md`), a
  16-pin USB 2.0 receptacle that sits on the board surface (3.26 mm tall) with its shell legs
  in four plated slots.  It is on the back at the rear edge, where the case leaves about
  17 mm under the board, so a mid-mount part is not needed.  The footprint is drawn from the
  datasheet's recommended layout (`usb_c()` in `gen_fp.py`), front flush with the board edge.
  KiCad has no 3D model for it; the footprint shows GCT's USB4105 instead, which has the
  same land pattern 3.65 mm nearer the edge, so the renders look right.
- The CH446Q footprint is KiCad's generic LQFP-44 10 x 10 mm; check it against the WCH drawing.

## The board

`tools/gen_pcb.py` made the first `C128-keyboard-rev3.kicad_pcb` straight from the schematic
netlist, the way Update PCB from Schematic would (every footprint carries its symbol's sheet
path and UUID), and `kicad-cli pcb drc --schematic-parity` reports no parity issues.  It runs
under KiCad's own python, because it needs the pcbnew module:

```
/Applications/KiCad/KiCad.app/Contents/Frameworks/Python.framework/Versions/Current/bin/python3 pcb/tools/gen_pcb.py
```

It refuses to overwrite an existing board (`--force` to start over): from here the board is
hand-edited, and schematic changes come in through Update PCB from Schematic (F8).

What it set up:

- **Outline** from `layout/outline.json`, the rev 2.3 Edge.Cuts unchanged (including the
  6.25 mm hole in the spacebar tab).  1.6 mm, four layers: signals on F.Cu and B.Cu, a
  GND plane on In1.Cu and a 5V_SYS plane on In2.Cu, each a zone over the whole board.  The
  script leaves them unfilled (pcbnew's filler crashes on a board built in memory);
  `route_keys.py` fills them.
- **Switches** on the rev 2.3 centers.  Rev 2.3 turned 14 top-row switches by 180 degrees;
  with an LED in every pocket that would light those keys from the top and the rest from the
  bottom, so rev 3 lines them all up (pins north, LED south, like the rev 2.3 lock keys).
  Keypad Enter keeps -90.  `UNIFORM_180` in the script.
- **Per key:** LED on the front in the pocket; diode (anode toward switch pin 2) and the
  LED's 100n on the back, behind the pocket.  Their references are on B.Fab: under the plate
  nobody reads them.  The LED chain snakes through the rows (`layout.led_chain`: lock keys
  first, then row 0 left to right, row 1 right to left, ...), and each LED is turned so data
  comes in on its upstream side; the 100n is turned to match its power pads.
- **Electronics** on the back in the three switch-free pockets of the top row, which have no
  holes on the back: x 183-225 (MCU, USB-C, LDO, buttons), x 297-340 at rev 2.3's FFC
  (host connector, CH446Q, FETs, LED buffer, keyboard-side fuse and diode), x 411-430
  (the five GPIO-column resistors, next to the keypad columns they drive).  The 74HC154
  and its 15 resistors sit mid-board at x 227-274 in the channel under the top row, which
  is clear of holes on the back the whole width (y 97.5-113).  First pass, packed by
  courtyard; no overlaps.  (These x values are in the generator's frame, before the move
  onto the sheet; see *Routing*.)
- **Rules** in the project file: net class Power (0.5 mm) for GND, +5V_KB, +5V_KB_F,
  +5V_SYS, +3V3 and VBUS; Default 0.25 mm, 0.6/0.3 mm vias; JLCPCB minimums.
  `C128-keyboard-rev3.kicad_dru` adds one custom rule: J1's own pads may sit 0.15 mm from
  its locating-peg holes, as the USB-C datasheet's land pattern has them (0.165 mm), under
  the board's 0.25 mm hole clearance.

Changed since that first pass, by hand and with `move.py`: the ESP32 was turned 180 degrees
so its GND row faces the rear edge and its GPIOs face the parts they drive (the GPIO plan in
`gen_sch.py` was re-picked to suit), and the LED buffer moved next to it; the 20 column
resistors are gone, since the key diodes already keep the columns apart (see the circuit
walkthrough); the silkscreen was cleared with `silk.py`; and the board was moved onto an A3
sheet with `to_sheet.py`.

## Routing

Status: routed completely (2026-11-23) by the steps below, several router passes and the
last few connections by hand, then `tidy.py` and `silk.py`.

`tools/route_keys.py` (KiCad's python, like `gen_pcb.py`) lays the copper every key shares,
in the switch's frame, and keeps it in one group, `route_keys`, that the next run replaces:

- switch pin 2 to the diode anode on B.Cu, past the east side of the center hole
- each LED power pad to a via (below the bottom-left pad, east of the top-right one), and
  both vias to the 100n on B.Cu
- the data hop to the next LED on F.Cu along the LED center line, where the two keys are
  neighbours in a row; hops around the lock keys, between rows and at the row ends are
  left for the router

It lays 91 switch-to-diode links, 92 LED power pairs and 75 data hops, with no DRC
copper errors.  It refills the planes after laying its vias, so every LED pad reaches GND or
5V_SYS through them.  Its copper is locked, so the autorouter treats it as fixed wiring.

`tools/freeroute.py` routes the rest with Freerouting 2.5.0 in a container (the
`freerouting` service in `docker-compose.yml`, built from `freerouting/Dockerfile`, jar pinned
by checksum): it exports the board to Specctra DSN in `freerouting/out/` (not committed),
runs the router headless, imports the session and refills the planes.  It changes the board
in place, so commit first; `git checkout` is the undo.

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
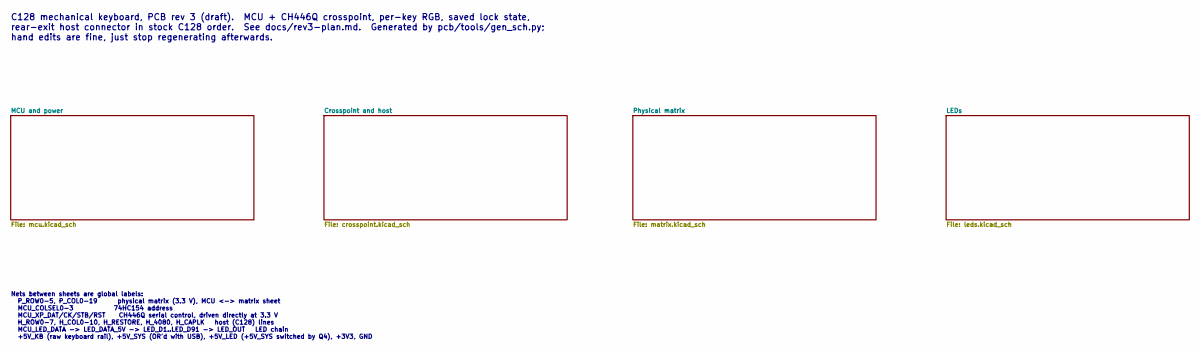
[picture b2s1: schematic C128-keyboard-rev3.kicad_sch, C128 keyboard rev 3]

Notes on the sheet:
C128 mechanical keyboard, PCB rev 3 (draft). MCU + CH446Q crosspoint, per-key RGB, saved lock state, rear-exit host connector in stock C128 order. See docs/rev3-plan.md. Generated by pcb/tools/gen_sch.py; hand edits are fine, just stop regenerating afterwards.
Nets between sheets are global labels: P_ROW0-5, P_COL0-19 physical matrix (3.3 V), MCU <-> matrix sheet MCU_COLSEL0-3 74HC154 address MCU_XP_DAT/CK/STB/RST CH446Q serial control, driven directly at 3.3 V H_ROW0-7, H_COL0-10, H_RESTORE, H_4080, H_CAPLK host (C128) lines MCU_LED_DATA -> LED_DATA_5V 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
